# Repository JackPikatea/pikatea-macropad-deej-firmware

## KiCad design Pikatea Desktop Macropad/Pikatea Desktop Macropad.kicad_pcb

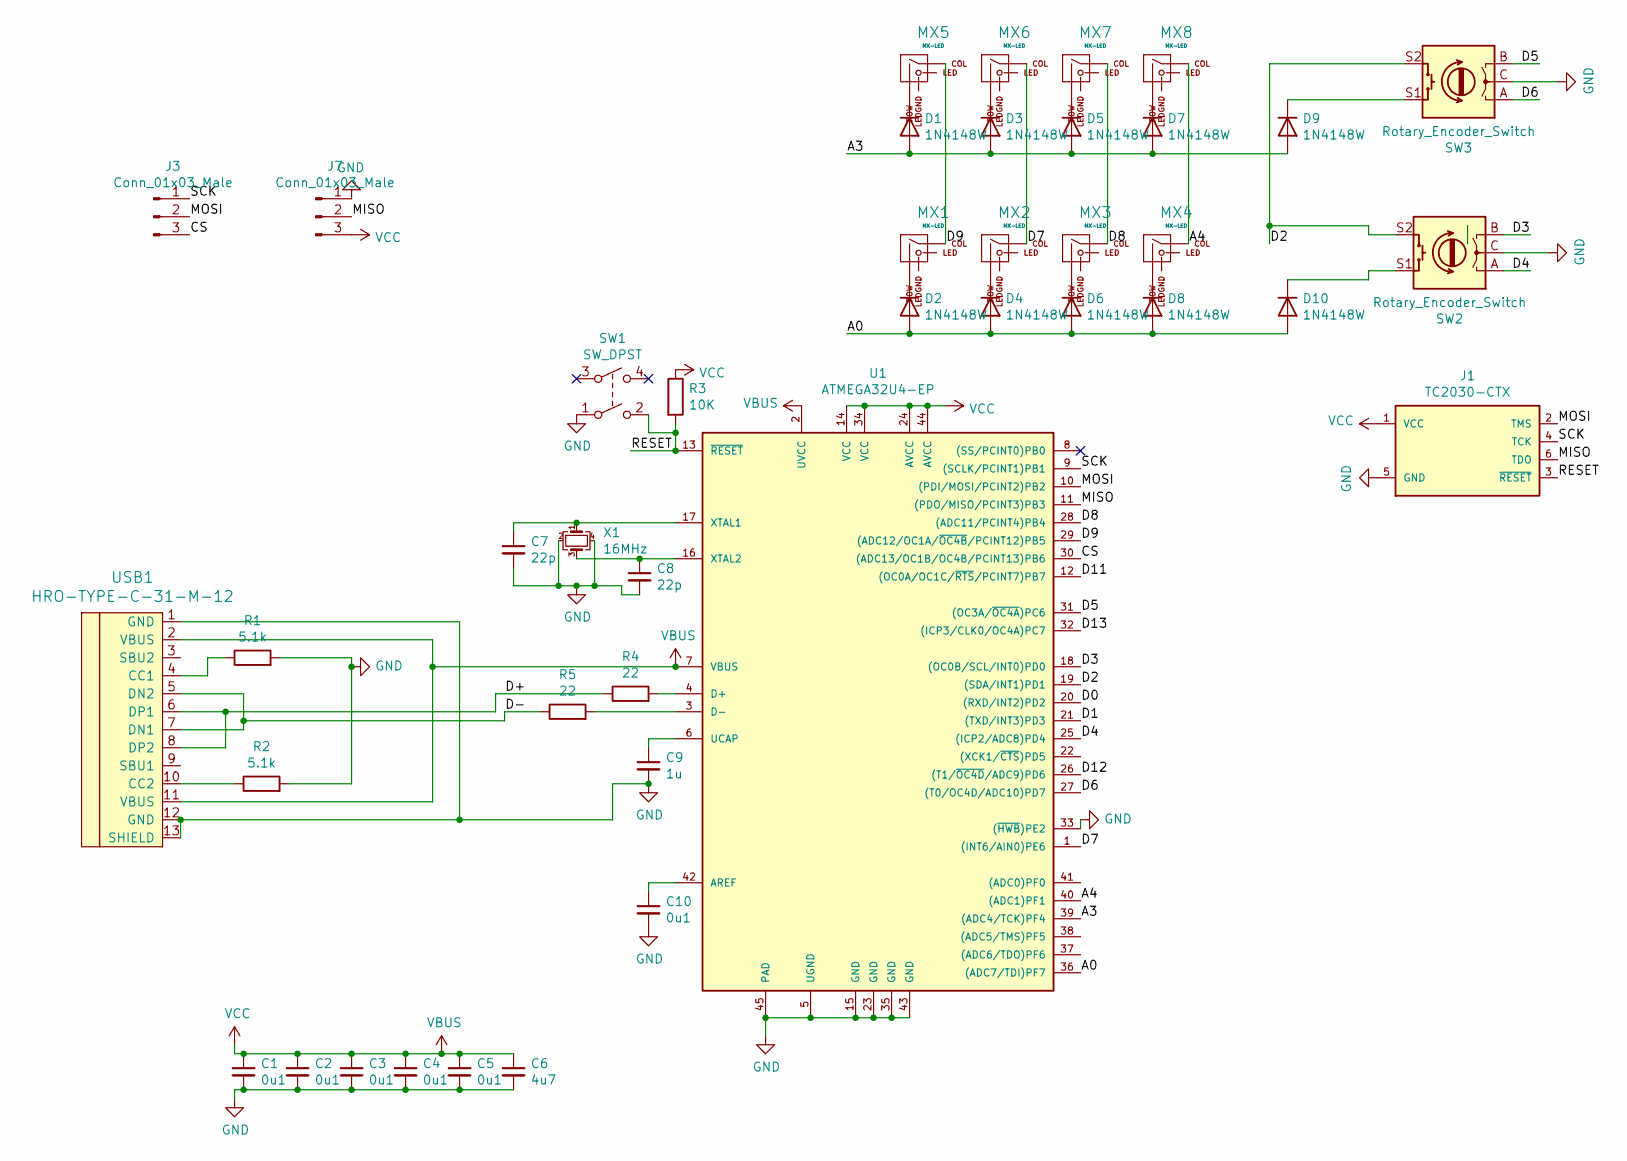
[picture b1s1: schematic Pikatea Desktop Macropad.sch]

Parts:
C1, C2, C3, C4, C5, C10: 0u1; C_0805_2012Metric
C6: 4u7; C_0805_2012Metric
C7, C8: 22p; C_0805_2012Metric
C9: 1u; C_0805_2012Metric
D1, D2, D3, D4, D5, D6, D7, D8, D9, D10: 1N4148W; D_SOD-123
J1: TC2030-CTX; TC2030-IDC
J3, J7: Conn_01x03_Male; PinHeader_1x03_P2.54mm_Vertical
MX1, MX2, MX3, MX4, MX5, MX6, MX7, MX8: MX-LED; MXOnly-1U
R1, R2: 5.1k; R_0805_2012Metric
R3: 10K; R_0805_2012Metric
R4, R5: 22; R_0805_2012Metric
SW1: SW_DPST; SW_SPST_TL3342
SW2, SW3: Rotary_Encoder_Switch; Encoder-BI_EN11_HSM0E
U1: ATMEGA32U4-EP; LQFP-44_10x10mm_P0.8mm
USB1: HRO-TYPE-C-31-M-12; HRO-TYPE-C-31-M-12-Assembly
X1: 16MHz; Crystal_SMD_SeikoEpson_FA238-4Pin_3.2x2.5mm

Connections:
/A0: D2.2 (A), D4.2 (A), D6.2 (A), D8.2 (A), D10.2 (A), U1.36 ((ADC7/TDI)PF7)
/A3: D1.2 (A), D3.2 (A), D5.2 (A), D7.2 (A), D9.2 (A), U1.39 ((ADC4/TCK)PF4)
/A4: MX4.1 (COL), MX8.1 (COL), U1.40 ((ADC1)PF1)
/CS: J3.3, U1.30 ((ADC13/OC1B/OC4B/PCINT13)PB6)
/D0: U1.20 ((RXD/INT2)PD2)
/D1: U1.21 ((TXD/INT3)PD3)
/D2: SW2.S2, SW3.S2, U1.19 ((SDA/INT1)PD1)
/D3: SW2.B, U1.18 ((OC0B/SCL/INT0)PD0)
/D4: SW2.A, U1.25 ((ICP2/ADC8)PD4)
/D5: SW3.B, U1.31 ((OC3A/~OC4A~)PC6)
/D6: SW3.A, U1.27 ((T0/OC4D/ADC10)PD7)
/D7: MX2.1 (COL), MX6.1 (COL), U1.1 ((INT6/AIN0)PE6)
/D8: MX3.1 (COL), MX7.1 (COL), U1.28 ((ADC11/PCINT4)PB4)
/D9: MX1.1 (COL), MX5.1 (COL), U1.29 ((ADC12/OC1A/~OC4B~/PCINT12)PB5)
/D11: U1.12 ((OC0A/OC1C/~RTS~/PCINT7)PB7)
/D12: U1.26 ((T1/~OC4D~/ADC9)PD6)
/D13: U1.32 ((ICP3/CLK0/OC4A)PC7)
/D+: R4.1, USB1.6 (DP1), USB1.8 (DP2)
/D-: R5.1, USB1.5 (DN2), USB1.7 (DN1)
/MISO: J1.6 (TDO), J7.2, U1.11 ((PDO/MISO/PCINT3)PB3)
/MOSI: J1.2 (TMS), J3.2, U1.10 ((PDI/MOSI/PCINT2)PB2)
/RESET: J1.3 (~RESET), R3.2, SW1.2, U1.13 (~RESET~)
/SCK: J1.4 (TCK), J3.1, U1.9 ((SCLK/PCINT1)PB1)
GND: C1.2, C2.2, C3.2, C4.2, C5.2, C6.2, C7.2, C8.2, C9.2, C10.2, J1.5 (GND), J7.1, R1.2, R2.2, SW1.1, SW2.C, SW3.C, U1.5 (UGND), U1.15 (GND), U1.23 (GND), U1.33 ((~HWB~)PE2), U1.35 (GND), U1.43 (GND), U1.45 (PAD), USB1.1 (GND), USB1.12 (GND), USB1.13 (SHIELD), X1.2, X1.4
unnamed: C7.1, U1.17 (XTAL1), X1.1
unnamed: C8.1, U1.16 (XTAL2), X1.3
unnamed: C9.1, U1.6 (UCAP)
unnamed: C10.1, U1.42 (AREF)
unnamed: D1.1 (K), MX5.2 (ROW)
unnamed: D2.1 (K), MX1.2 (ROW)
unnamed: D3.1 (K), MX6.2 (ROW)
unnamed: D4.1 (K), MX2.2 (ROW)
unnamed: D5.1 (K), MX7.2 (ROW)
unnamed: D6.1 (K), MX3.2 (ROW)
unnamed: D7.1 (K), MX8.2 (ROW)
unnamed: D8.1 (K), MX4.2 (ROW)
unnamed: D9.1 (K), SW3.S1
unnamed: D10.1 (K), SW2.S1
unnamed: R1.1, USB1.4 (CC1)
unnamed: R2.1, USB1.10 (CC2)
unnamed: R4.2, U1.4 (D+)
unnamed: R5.2, U1.3 (D-)
VBUS: C1.1, C2.1, C3.1, C4.1, C5.1, C6.1, J1.1 (VCC), J7.3, R3.1, U1.2 (UVCC), U1.7 (VBUS), U1.14 (VCC), U1.24 (AVCC), U1.34 (VCC), U1.44 (AVCC), USB1.2 (VBUS), USB1.11 (VBUS)

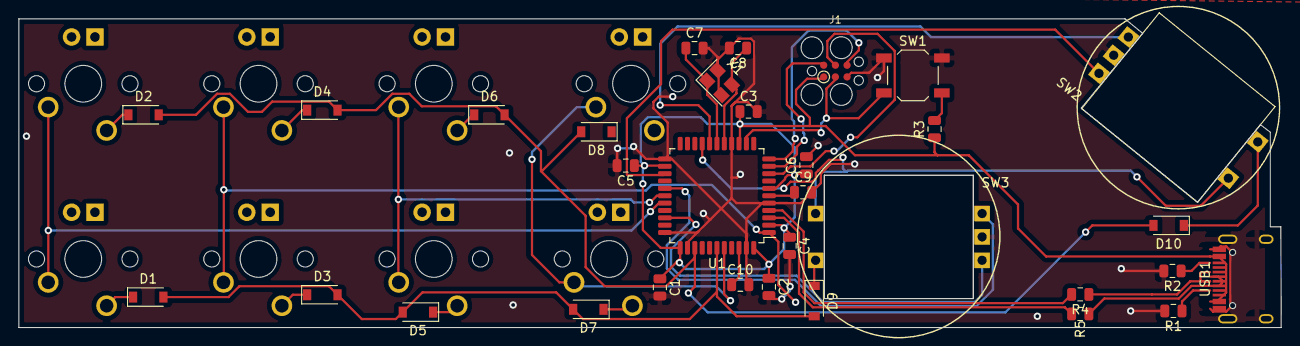
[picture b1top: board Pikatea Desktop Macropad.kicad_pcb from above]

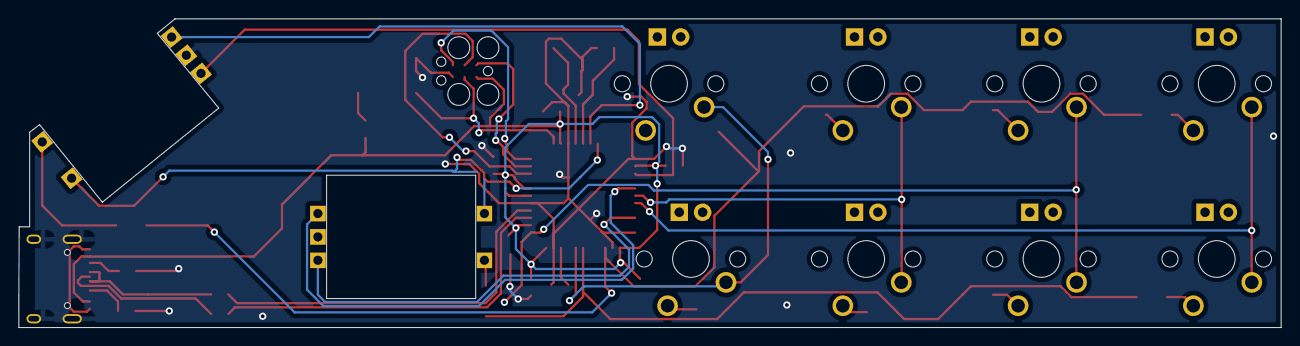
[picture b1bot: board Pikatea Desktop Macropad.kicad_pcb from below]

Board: 2 copper layers, 137.2 x 33.5 mm, 40 parts (8 on the bottom side), 37 nets.

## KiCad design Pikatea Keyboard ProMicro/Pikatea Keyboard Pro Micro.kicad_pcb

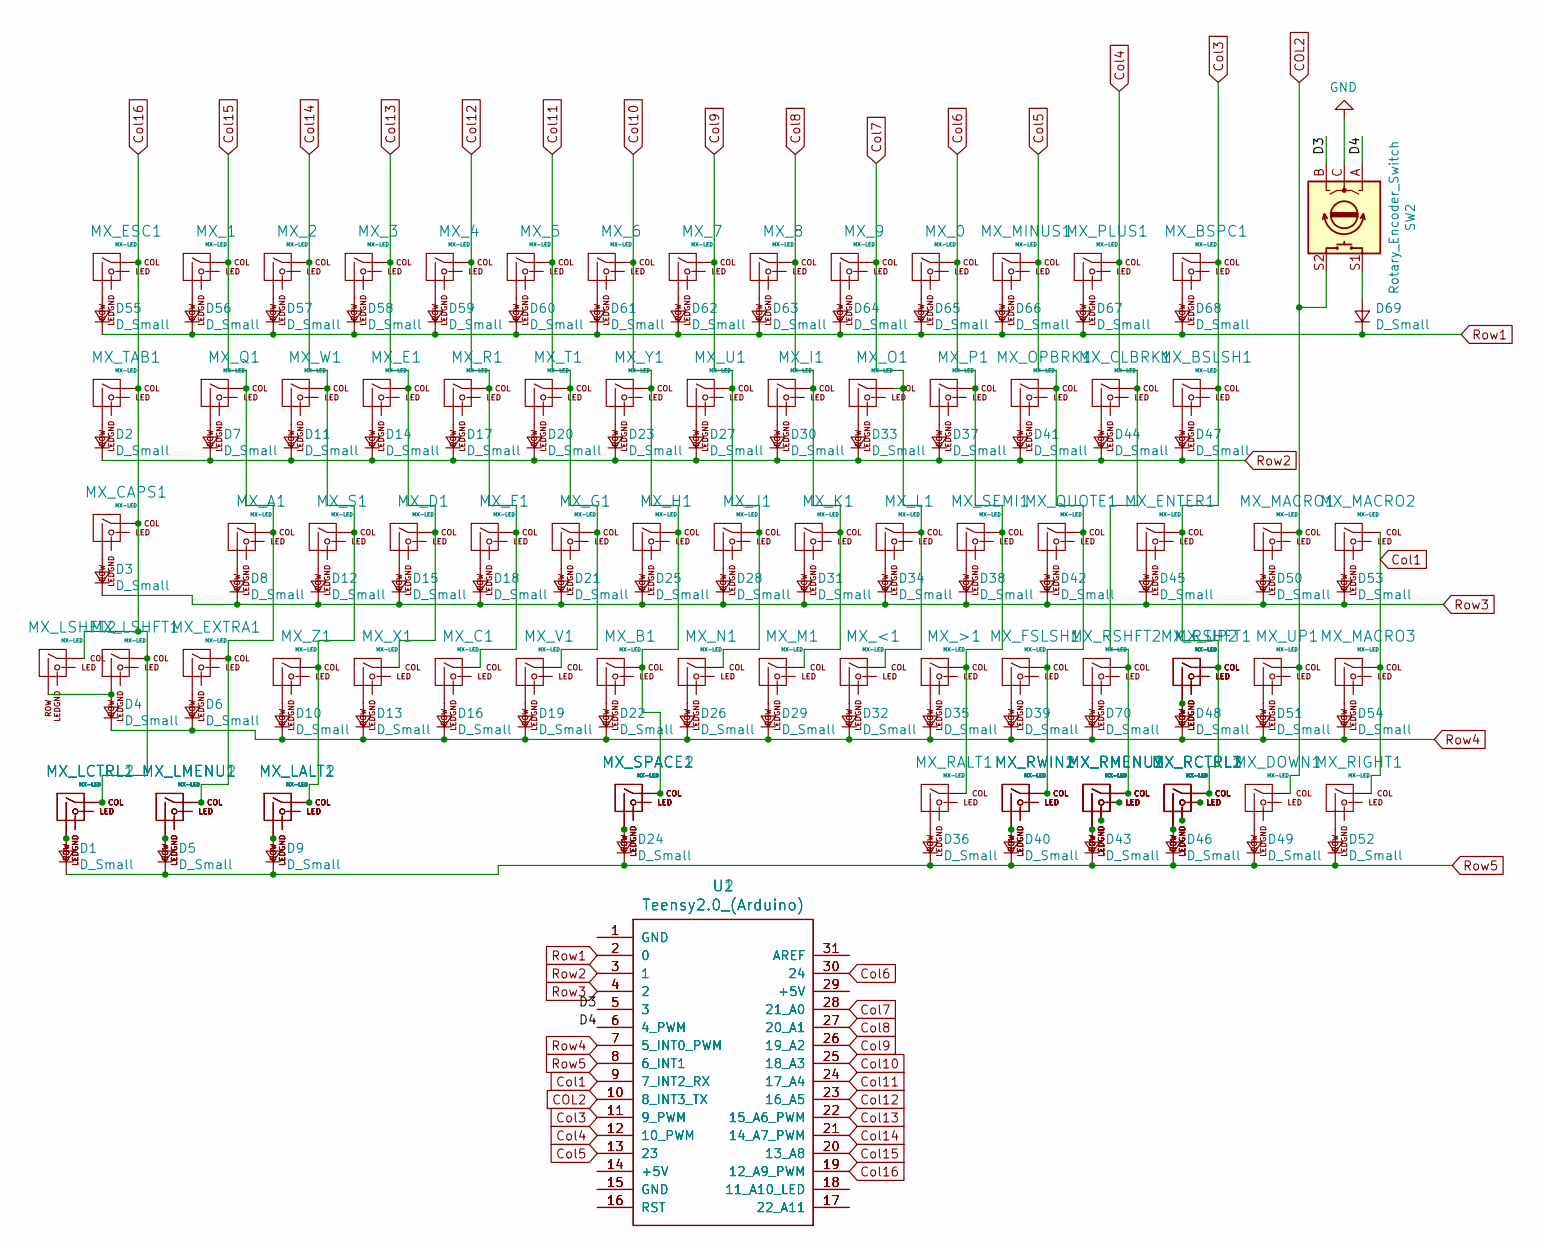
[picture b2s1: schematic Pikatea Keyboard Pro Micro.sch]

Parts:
D1, D2, D3, D4, D5, D6, D7, D8, D9, D10, D11, D12, D13, D14, D15, D16, D17, D18, D19, D20, D21, D22, D23, D24, D25, D26, D27, D28, D29, D30, D31, D32, D33, D34, D35, D36, D37, D38, D39, D40, D41, D42, D43, D44, D45, D46, D47, D48, D49, D50, D51, D52, D53, D54, D55, D56, D57, D58, D59, D60, D61, D62, D63, D64, D65, D66, D67, D68, D69, D70: D_Small; D_SOD-123
MX_0, MX_3, MX_4, MX_5, MX_6, MX_7, MX_8, MX_9: MX-LED; MXOnly-1U
MX_1, MX_2: MX-LED; MXOnly-1U-FLIPPED
MX_<1: MX-LED; MXOnly-1U
MX_>1: MX-LED; MXOnly-1U
MX_A1: MX-LED; MXOnly-1U-FLIPPED
MX_B1: MX-LED; MXOnly-1U
MX_BSLSH1: MX-LED; MXOnly-1.5U-FLIPPED
MX_BSPC1: MX-LED; MXOnly-2U-FLIPPED
MX_C1: MX-LED; MXOnly-1U
MX_CAPS1: MX-LED; MXOnly-1.75U-FLIPPED
MX_CLBRK1: MX-LED; MXOnly-1U
MX_D1: MX-LED; MXOnly-1U
MX_DOWN1: MX-LED; MXOnly-1U
MX_E1: MX-LED; MXOnly-1U
MX_ENTER1: MX-LED; MXOnly-2.25U-FLIPPED-ReversedStabilizers
MX_ESC1: MX-LED; MXOnly-1U-FLIPPED
MX_EXTRA1: MX-LED; MXOnly-1U-FLIPPED
MX_F1: MX-LED; MXOnly-1U
MX_FSLSH1: MX-LED; MXOnly-1U
MX_G1: MX-LED; MXOnly-1U
MX_H1: MX-LED; MXOnly-1U
MX_I1: MX-LED; MXOnly-1U
MX_J1: MX-LED; MXOnly-1U
MX_K1: MX-LED; MXOnly-1U
MX_L1: MX-LED; MXOnly-1U
MX_LALT1: MX-LED; MXOnly-1.25U-FLIPPED
MX_LALT2: MX-LED; MXOnly-1.5U-FLIPPED
MX_LCTRL1: MX-LED; MXOnly-1.25U-FLIPPED
MX_LCTRL2: MX-LED; MXOnly-1.5U-FLIPPED
MX_LMENU1: MX-LED; MXOnly-1.25U-FLIPPED
MX_LMENU2: MX-LED; MXOnly-1U-FLIPPED
MX_LSHFT1: MX-LED; MXOnly-2.25U-FLIPPED-ReversedStabilizers
MX_LSHFT2: MX-LED; MXOnly-1.25U-FLIPPED
MX_M1: MX-LED; MXOnly-1U
MX_MACRO1, MX_MACRO2, MX_MACRO3: MX-LED; MXOnly-1U
MX_MINUS1: MX-LED; MXOnly-1U
MX_N1: MX-LED; MXOnly-1U
MX_O1: MX-LED; MXOnly-1U
MX_OPBRK1: MX-LED; MXOnly-1U
MX_P1: MX-LED; MXOnly-1U
MX_PLUS1: MX-LED; MXOnly-1U
MX_Q1: MX-LED; MXOnly-1U-FLIPPED
MX_QUOTE1: MX-LED; MXOnly-1U
MX_R1: MX-LED; MXOnly-1U
MX_RALT1: MX-LED; MXOnly-1.25U-FLIPPED
MX_RCTRL1: MX-LED; MXOnly-1.25U-FLIPPED
MX_RCTRL2: MX-LED; MXOnly-1.5U-FLIPPED
MX_RCTRL3: MX-LED; MXOnly-1U
MX_RIGHT1: MX-LED; MXOnly-1U
MX_RMENU1: MX-LED; MXOnly-1.25U-FLIPPED
MX_RMENU2: MX-LED; MXOnly-1.5U-FLIPPED
MX_RMENU3: MX-LED; MXOnly-1U-FLIPPED
MX_RSHFT1: MX-LED; MXOnly-2.75U-FLIPPED-ReversedStabilizers
MX_RSHFT2: MX-LED; MXOnly-1.75U-FLIPPED
MX_RWIN1: MX-LED; MXOnly-1.25U-FLIPPED
MX_RWIN2: MX-LED; MXOnly-1U-FLIPPED
MX_S1: MX-LED; MXOnly-1U
MX_SEMI1: MX-LED; MXOnly-1U
MX_SPACE1: MX-LED; MXOnly-6.25U-FLIPPED-ReversedStabilizers
MX_SPACE2: MX-LED; MXOnly-7U-FLIPPED-ReversedStabilizers
MX_T1: MX-LED; MXOnly-1U
MX_TAB1: MX-LED; MXOnly-1.5U-FLIPPED
MX_U1: MX-LED; MXOnly-1U
MX_UP1, MX_UP2: MX-LED; MXOnly-1U
MX_V1: MX-LED; MXOnly-1U
MX_W1: MX-LED; MXOnly-1U
MX_X1: MX-LED; MXOnly-1U
MX_Y1: MX-LED; MXOnly-1U
MX_Z1: MX-LED; MXOnly-1U
SW2: Rotary_Encoder_Switch; Encoder-BI_EN11_HSM0E
U1, U2: Teensy2.0_(Arduino); Teensy2.0

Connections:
/D3: SW2.B, U1.5 (3), U2.5 (3)
/D4: SW2.A, U1.6 (4_PWM), U2.6 (4_PWM)
COL2: MX_DOWN1.1 (COL), MX_MACRO1.1 (COL), MX_UP1.1 (COL), SW2.S2, U1.10 (8_INT3_TX), U2.10 (8_INT3_TX)
Col1: MX_MACRO2.1 (COL), MX_MACRO3.1 (COL), MX_RIGHT1.1 (COL), U1.9 (7_INT2_RX), U2.9 (7_INT2_RX)
Col3: MX_BSLSH1.1 (COL), MX_BSPC1.1 (COL), MX_ENTER1.1 (COL), MX_RCTRL1.1 (COL), MX_RCTRL2.1 (COL), MX_RCTRL3.1 (COL), MX_RSHFT1.1 (COL), MX_UP2.1 (COL), U1.11 (9_PWM), U2.11 (9_PWM)
Col4: MX_CLBRK1.1 (COL), MX_PLUS1.1 (COL), MX_RMENU1.1 (COL), MX_RMENU2.1 (COL), MX_RMENU3.1 (COL), MX_RSHFT2.1 (COL), U1.12 (10_PWM), U2.12 (10_PWM)
Col5: MX_FSLSH1.1 (COL), MX_MINUS1.1 (COL), MX_OPBRK1.1 (COL), MX_QUOTE1.1 (COL), MX_RWIN1.1 (COL), MX_RWIN2.1 (COL), U1.13 (23), U2.13 (23)
Col6: MX_0.1 (COL), MX_>1.1 (COL), MX_P1.1 (COL), MX_RALT1.1 (COL), MX_SEMI1.1 (COL), U1.30 (24), U2.30 (24)
Col7: MX_9.1 (COL), MX_<1.1 (COL), MX_L1.1 (COL), MX_O1.1 (COL), U1.28 (21_A0), U2.28 (21_A0)
Col8: MX_8.1 (COL), MX_I1.1 (COL), MX_K1.1 (COL), MX_M1.1 (COL), U1.27 (20_A1), U2.27 (20_A1)
Col9: MX_7.1 (COL), MX_J1.1 (COL), MX_N1.1 (COL), MX_U1.1 (COL), U1.26 (19_A2), U2.26 (19_A2)
Col10: MX_6.1 (COL), MX_B1.1 (COL), MX_H1.1 (COL), MX_SPACE1.1 (COL), MX_SPACE2.1 (COL), MX_Y1.1 (COL), U1.25 (18_A3), U2.25 (18_A3)
Col11: MX_5.1 (COL), MX_G1.1 (COL), MX_T1.1 (COL), MX_V1.1 (COL), U1.24 (17_A4), U2.24 (17_A4)
Col12: MX_4.1 (COL), MX_C1.1 (COL), MX_F1.1 (COL), MX_R1.1 (COL), U1.23 (16_A5), U2.23 (16_A5)
Col13: MX_3.1 (COL), MX_D1.1 (COL), MX_E1.1 (COL), MX_X1.1 (COL), U1.22 (15_A6_PWM), U2.22 (15_A6_PWM)
Col14: MX_2.1 (COL), MX_LALT1.1 (COL), MX_LALT2.1 (COL), MX_S1.1 (COL), MX_W1.1 (COL), MX_Z1.1 (COL), U1.21 (14_A7_PWM), U2.21 (14_A7_PWM)
Col15: MX_1.1 (COL), MX_A1.1 (COL), MX_EXTRA1.1 (COL), MX_LMENU1.1 (COL), MX_LMENU2.1 (COL), MX_Q1.1 (COL), U1.20 (13_A8), U2.20 (13_A8)
Col16: MX_CAPS1.1 (COL), MX_ESC1.1 (COL), MX_LCTRL1.1 (COL), MX_LCTRL2.1 (COL), MX_LSHFT1.1 (COL), MX_LSHFT2.1 (COL), MX_TAB1.1 (COL), U1.19 (12_A9_PWM), U2.19 (12_A9_PWM)
GND: SW2.C
unnamed: D1.2 (A), MX_LCTRL1.2 (ROW), MX_LCTRL2.2 (ROW)
unnamed: D2.2 (A), MX_TAB1.2 (ROW)
unnamed: D3.2 (A), MX_CAPS1.2 (ROW)
unnamed: D4.2 (A), MX_LSHFT1.2 (ROW), MX_LSHFT2.2 (ROW)
unnamed: D5.2 (A), MX_LMENU1.2 (ROW), MX_LMENU2.2 (ROW)
unnamed: D6.2 (A), MX_EXTRA1.2 (ROW)
unnamed: D7.2 (A), MX_Q1.2 (ROW)
unnamed: D8.2 (A), MX_A1.2 (ROW)
unnamed: D9.2 (A), MX_LALT1.2 (ROW), MX_LALT2.2 (ROW)
unnamed: D10.2 (A), MX_Z1.2 (ROW)
unnamed: D11.2 (A), MX_W1.2 (ROW)
unnamed: D12.2 (A), MX_S1.2 (ROW)
unnamed: D13.2 (A), MX_X1.2 (ROW)
unnamed: D14.2 (A), MX_E1.2 (ROW)
unnamed: D15.2 (A), MX_D1.2 (ROW)
unnamed: D16.2 (A), MX_C1.2 (ROW)
unnamed: D17.2 (A), MX_R1.2 (ROW)
unnamed: D18.2 (A), MX_F1.2 (ROW)
unnamed: D19.2 (A), MX_V1.2 (ROW)
unnamed: D20.2 (A), MX_T1.2 (ROW)
unnamed: D21.2 (A), MX_G1.2 (ROW)
unnamed: D22.2 (A), MX_B1.2 (ROW)
unnamed: D23.2 (A), MX_Y1.2 (ROW)
unnamed: D24.2 (A), MX_SPACE1.2 (ROW), MX_SPACE2.2 (ROW)
unnamed: D25.2 (A), MX_H1.2 (ROW)
unnamed: D26.2 (A), MX_N1.2 (ROW)
unnamed: D27.2 (A), MX_U1.2 (ROW)
unnamed: D28.2 (A), MX_J1.2 (ROW)
unnamed: D29.2 (A), MX_M1.2 (ROW)
unnamed: D30.2 (A), MX_I1.2 (ROW)
unnamed: D31.2 (A), MX_K1.2 (ROW)
unnamed: D32.2 (A), MX_<1.2 (ROW)
unnamed: D33.2 (A), MX_O1.2 (ROW)
unnamed: D34.2 (A), MX_L1.2 (ROW)
unnamed: D35.2 (A), MX_>1.2 (ROW)
unnamed: D36.2 (A), MX_RALT1.2 (ROW)
unnamed: D37.2 (A), MX_P1.2 (ROW)
unnamed: D38.2 (A), MX_SEMI1.2 (ROW)
unnamed: D39.2 (A), MX_FSLSH1.2 (ROW)
unnamed: D40.2 (A), MX_RWIN1.2 (ROW), MX_RWIN2.2 (ROW)
unnamed: D41.2 (A), MX_OPBRK1.2 (ROW)
unnamed: D42.2 (A), MX_QUOTE1.2 (ROW)
unnamed: D43.2 (A), MX_RMENU1.2 (ROW), MX_RMENU2.2 (ROW), MX_RMENU3.2 (ROW)
unnamed: D44.2 (A), MX_CLBRK1.2 (ROW)
unnamed: D45.2 (A), MX_ENTER1.2 (ROW)
unnamed: D46.2 (A), MX_RCTRL1.2 (ROW), MX_RCTRL2.2 (ROW), MX_RCTRL3.2 (ROW)
unnamed: D47.2 (A), MX_BSLSH1.2 (ROW)
unnamed: D48.2 (A), MX_RSHFT1.2 (ROW), MX_UP2.2 (ROW)
unnamed: D49.2 (A), MX_DOWN1.2 (ROW)
unnamed: D50.2 (A), MX_MACRO1.2 (ROW)
unnamed: D51.2 (A), MX_UP1.2 (ROW)
unnamed: D52.2 (A), MX_RIGHT1.2 (ROW)
unnamed: D53.2 (A), MX_MACRO2.2 (ROW)
unnamed: D54.2 (A), MX_MACRO3.2 (ROW)
unnamed: D55.2 (A), MX_ESC1.2 (ROW)
unnamed: D56.2 (A), MX_1.2 (ROW)
unnamed: D57.2 (A), MX_2.2 (ROW)
unnamed: D58.2 (A), MX_3.2 (ROW)
unnamed: D59.2 (A), MX_4.2 (ROW)
unnamed: D60.2 (A), MX_5.2 (ROW)
unnamed: D61.2 (A), MX_6.2 (ROW)
unnamed: D62.2 (A), MX_7.2 (ROW)
unnamed: D63.2 (A), MX_8.2 (ROW)
unnamed: D64.2 (A), MX_9.2 (ROW)
unnamed: D65.2 (A), MX_0.2 (ROW)
unnamed: D66.2 (A), MX_MINUS1.2 (ROW)
unnamed: D67.2 (A), MX_PLUS1.2 (ROW)
unnamed: D68.2 (A), MX_BSPC1.2 (ROW)
unnamed: D69.2 (A), SW2.S1
unnamed: D70.2 (A), MX_RSHFT2.2 (ROW)
unnamed: MX_LALT1.3 (LED), MX_LALT2.3 (LED)
unnamed: MX_LALT1.4 (LEDGND), MX_LALT2.4 (LEDGND)
unnamed: MX_LCTRL1.3 (LED), MX_LCTRL2.3 (LED)
unnamed: MX_LCTRL1.4 (LEDGND), MX_LCTRL2.4 (LEDGND)
unnamed: MX_LMENU1.3 (LED), MX_LMENU2.3 (LED)
unnamed: MX_LMENU1.4 (LEDGND), MX_LMENU2.4 (LEDGND)
unnamed: MX_RCTRL1.3 (LED), MX_RCTRL2.3 (LED), MX_RCTRL3.3 (LED)
unnamed: MX_RCTRL1.4 (LEDGND), MX_RCTRL2.4 (LEDGND), MX_RCTRL3.4 (LEDGND)
unnamed: MX_RMENU1.3 (LED), MX_RMENU2.3 (LED), MX_RMENU3.3 (LED)
unnamed: MX_RMENU1.4 (LEDGND), MX_RMENU2.4 (LEDGND), MX_RMENU3.4 (LEDGND)
unnamed: MX_RSHFT1.3 (LED), MX_UP2.3 (LED)
unnamed: MX_RSHFT1.4 (LEDGND), MX_UP2.4 (LEDGND)
unnamed: MX_RWIN1.3 (LED), MX_RWIN2.3 (LED)
unnamed: MX_RWIN1.4 (LEDGND), MX_RWIN2.4 (LEDGND)
unnamed: MX_SPACE1.3 (LED), MX_SPACE2.3 (LED)
unnamed: MX_SPACE1.4 (LEDGND), MX_SPACE2.4 (LEDGND)
unnamed: U1.1 (GND), U2.1 (GND)
unnamed: U1.14 (+5V), U2.14 (+5V)
unnamed: U1.15 (GND), U2.15 (GND)
unnamed: U1.16 (RST), U2.16 (RST)
unnamed: U1.17 (22_A11), U2.17 (22_A11)
unnamed: U1.18 (11_A10_LED), U2.18 (11_A10_LED)
unnamed: U1.29 (+5V), U2.29 (+5V)
unnamed: U1.31 (AREF), U2.31 (AREF)
Row1: D55.1 (K), D56.1 (K), D57.1 (K), D58.1 (K), D59.1 (K), D60.1 (K), D61.1 (K), D62.1 (K), D63.1 (K), D64.1 (K), D65.1 (K), D66.1 (K), D67.1 (K), D68.1 (K), D69.1 (K), U1.2 (0), U2.2 (0)
Row2: D2.1 (K), D7.1 (K), D11.1 (K), D14.1 (K), D17.1 (K), D20.1 (K), D23.1 (K), D27.1 (K), D30.1 (K), D33.1 (K), D37.1 (K), D41.1 (K), D44.1 (K), D47.1 (K), U1.3 (1), U2.3 (1)
Row3: D3.1 (K), D8.1 (K), D12.1 (K), D15.1 (K), D18.1 (K), D21.1 (K), D25.1 (K), D28.1 (K), D31.1 (K), D34.1 (K), D38.1 (K), D42.1 (K), D45.1 (K), D50.1 (K), D53.1 (K), U1.4 (2), U2.4 (2)
Row4: D4.1 (K), D6.1 (K), D10.1 (K), D13.1 (K), D16.1 (K), D19.1 (K), D22.1 (K), D26.1 (K), D29.1 (K), D32.1 (K), D35.1 (K), D39.1 (K), D48.1 (K), D51.1 (K), D54.1 (K), D70.1 (K), U1.7 (5_INT0_PWM), U2.7 (5_INT0_PWM)
Row5: D1.1 (K), D5.1 (K), D9.1 (K), D24.1 (K), D36.1 (K), D40.1 (K), D43.1 (K), D46.1 (K), D49.1 (K), D52.1 (K), U1.8 (6_INT1), U2.8 (6_INT1)

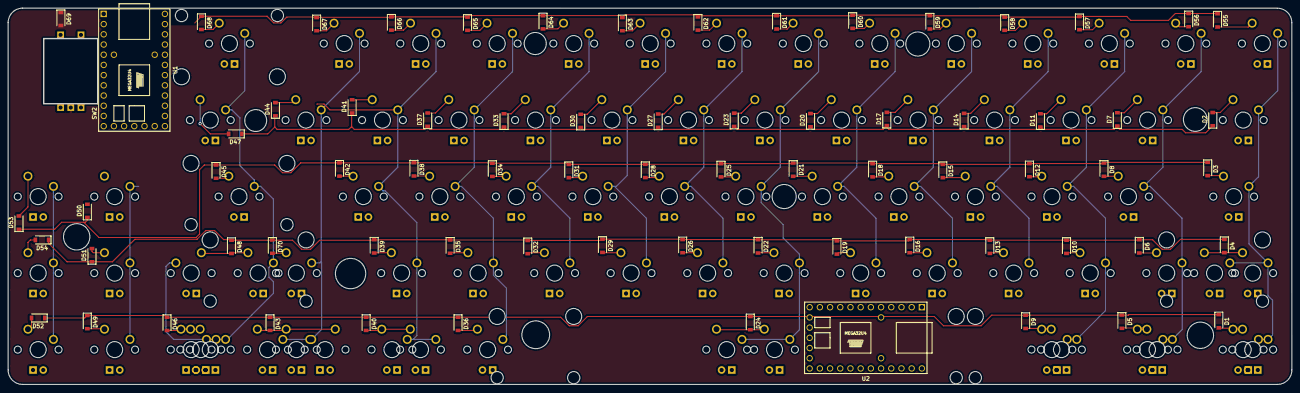
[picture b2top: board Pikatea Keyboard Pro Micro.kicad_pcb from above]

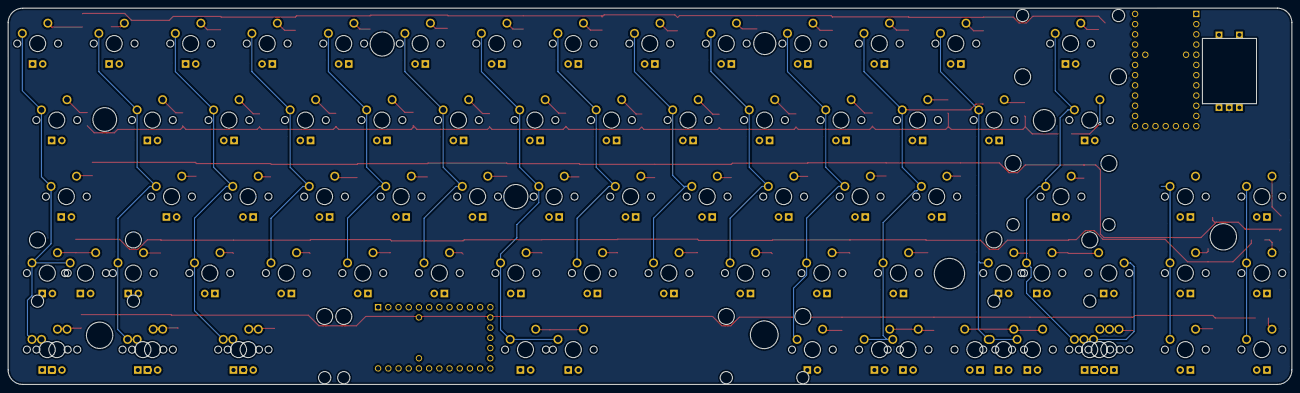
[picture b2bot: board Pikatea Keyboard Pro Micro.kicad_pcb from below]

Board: 2 copper layers, 319.6 x 93.7 mm, 153 parts (78 on the bottom side), 117 nets.

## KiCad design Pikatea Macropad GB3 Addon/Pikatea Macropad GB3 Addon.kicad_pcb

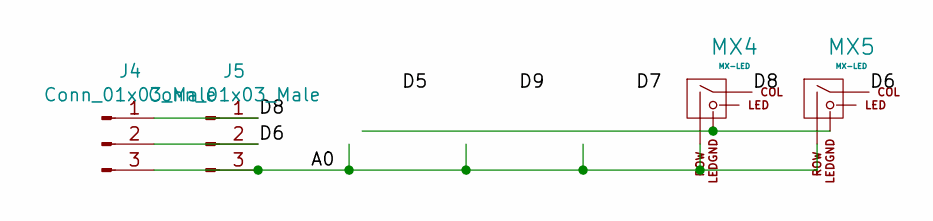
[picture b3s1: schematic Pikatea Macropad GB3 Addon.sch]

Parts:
J4, J5: Conn_01x03_Male; PinHeader_1x03_P2.54mm_Vertical
MX4, MX5: MX-LED; MXOnly-1U

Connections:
/A0: J4.3, J5.3, MX4.2 (ROW), MX5.2 (ROW)
/D6: J4.2, J5.2, MX5.1 (COL)
/D8: J4.1, J5.1, MX4.1 (COL)
unnamed: MX4.4 (LEDGND), MX5.4 (LEDGND)

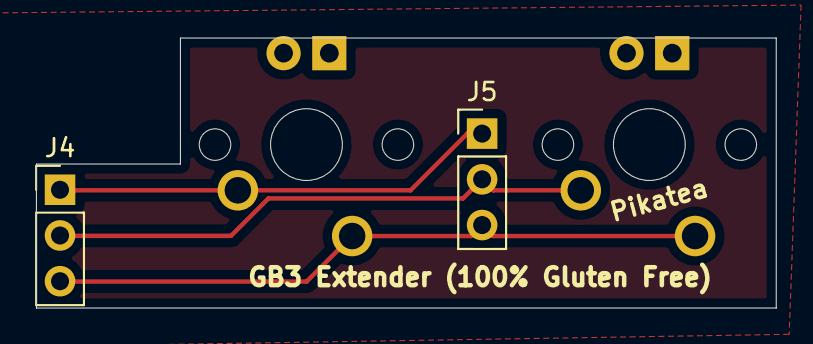
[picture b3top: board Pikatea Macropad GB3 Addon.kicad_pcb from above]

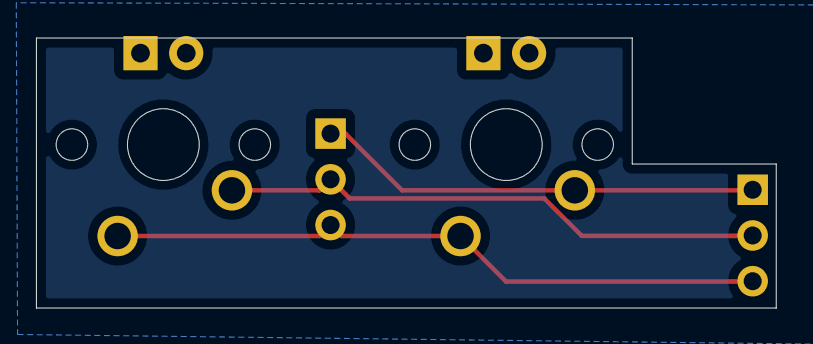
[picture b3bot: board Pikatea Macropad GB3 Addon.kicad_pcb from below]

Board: 2 copper layers, 41.1 x 15.0 mm, 4 parts (2 on the bottom side), 4 nets.

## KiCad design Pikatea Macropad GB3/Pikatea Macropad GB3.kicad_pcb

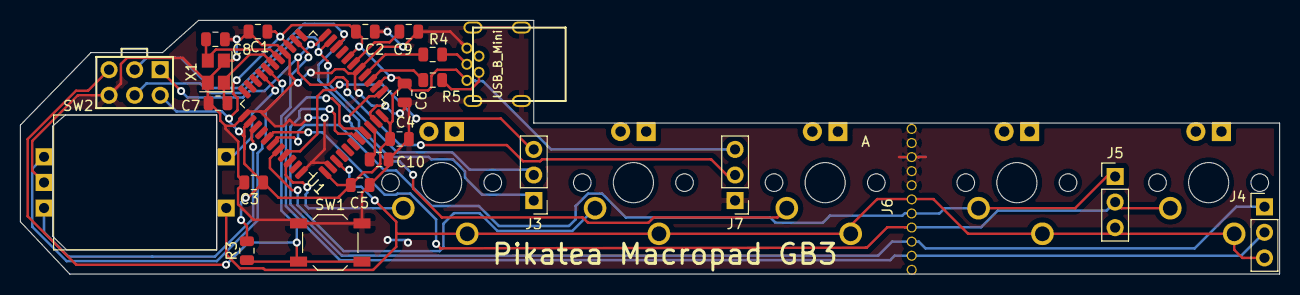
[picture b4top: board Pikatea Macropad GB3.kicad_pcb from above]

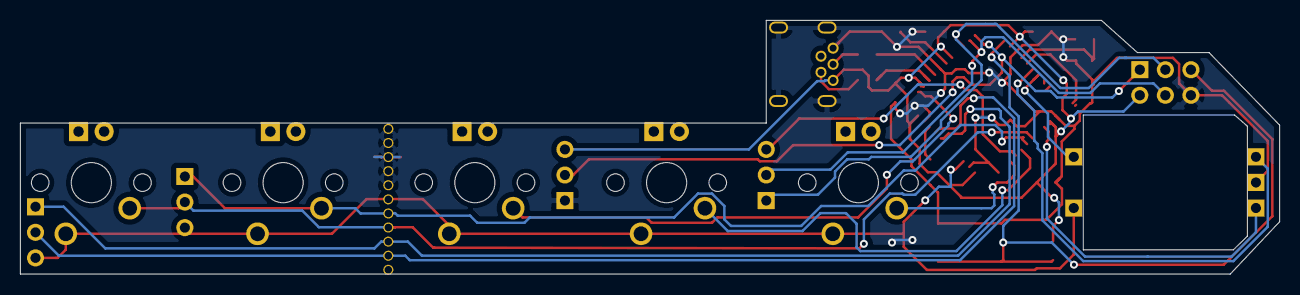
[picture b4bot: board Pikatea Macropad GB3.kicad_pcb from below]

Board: 2 copper layers, 125.1 x 25.2 mm, 29 parts (5 on the bottom side), 27 nets.

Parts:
C1, C2, C3, C4, C5, C10: 0u1; C_0805_2012Metric
C6: 4u7; C_0805_2012Metric
C7, C8: 22p; C_0805_2012Metric
C9: 1u; C_0805_2012Metric
J1: AVR-ISP-6; AVR_ICSP_3x2
J2: USB_B_Mini; USB-Mini-B_ LCSC-C46398
J3, J4, J5, J7: Conn_01x03_Male; PinHeader_1x03_P2.54mm_Vertical
J6: Conn_01x06_Male; Breakaway-Throughole
MX1, MX2, MX3, MX4, MX5: MX-LED; MXOnly-1U
R3: 10K; R_0805_2012Metric
R4, R5: 22; R_0805_2012Metric
SW1: SW_DPST; SW_SPST_TL3342
SW2: Rotary_Encoder_Switch; Encoder-BI_EN11_HSM0E
U1: ATMEGA32U4-EP; LQFP-44_10x10mm_P0.8mm
X1: 16MHz; Crystal_SMD_SeikoEpson_FA238-4Pin_3.2x2.5mm

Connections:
/A0: J4.3, J5.3, J6.4, MX1.2, MX2.2, MX3.2, MX4.2, MX5.2, SW2.S2, U1.36
/CS: J3.3, U1.30
/D0: J4.2, J6.6, U1.41
/D1: J4.1, J6.5, U1.40
/D2: SW2.S1, U1.19
/D3: SW2.B, U1.18
/D4: SW2.A, U1.25
/D5: MX1.1, U1.31
/D6: J5.2, J6.3, MX5.1, U1.27
/D7: MX3.1, U1.1
/D8: J5.1, J6.2, MX4.1, U1.28
/D9: MX2.1, U1.29
/D+: J2.3, R4.1
/D-: J2.2, R5.1
/MISO: J1.1, J7.2, U1.11
/MOSI: J1.4, J3.2, U1.10
/RESET: J1.5, R3.2, SW1.2, U1.13
/SCK: J1.3, J3.1, U1.9
GND: C1.2, C2.2, C3.2, C4.2, C5.2, C6.2, C7.2, C8.2, C9.2, C10.2, J1.6, J2.5, J2.6, J6.1, J7.1, SW1.1, SW2.C, U1.5, U1.15, U1.23, U1.33, U1.35, U1.43, X1.2, X1.4
unnamed: C7.1, U1.17, X1.1
unnamed: C8.1, U1.16, X1.3
unnamed: C9.1, U1.6
unnamed: C10.1, U1.42
unnamed: MX1.4, MX2.4, MX3.4, MX4.4, MX5.4
unnamed: R4.2, U1.4
unnamed: R5.2, U1.3
VBUS: C1.1, C2.1, C3.1, C4.1, C5.1, C6.1, J1.2, J2.1, J7.3, R3.1, U1.2, U1.7, U1.14, U1.24, U1.34, U1.44

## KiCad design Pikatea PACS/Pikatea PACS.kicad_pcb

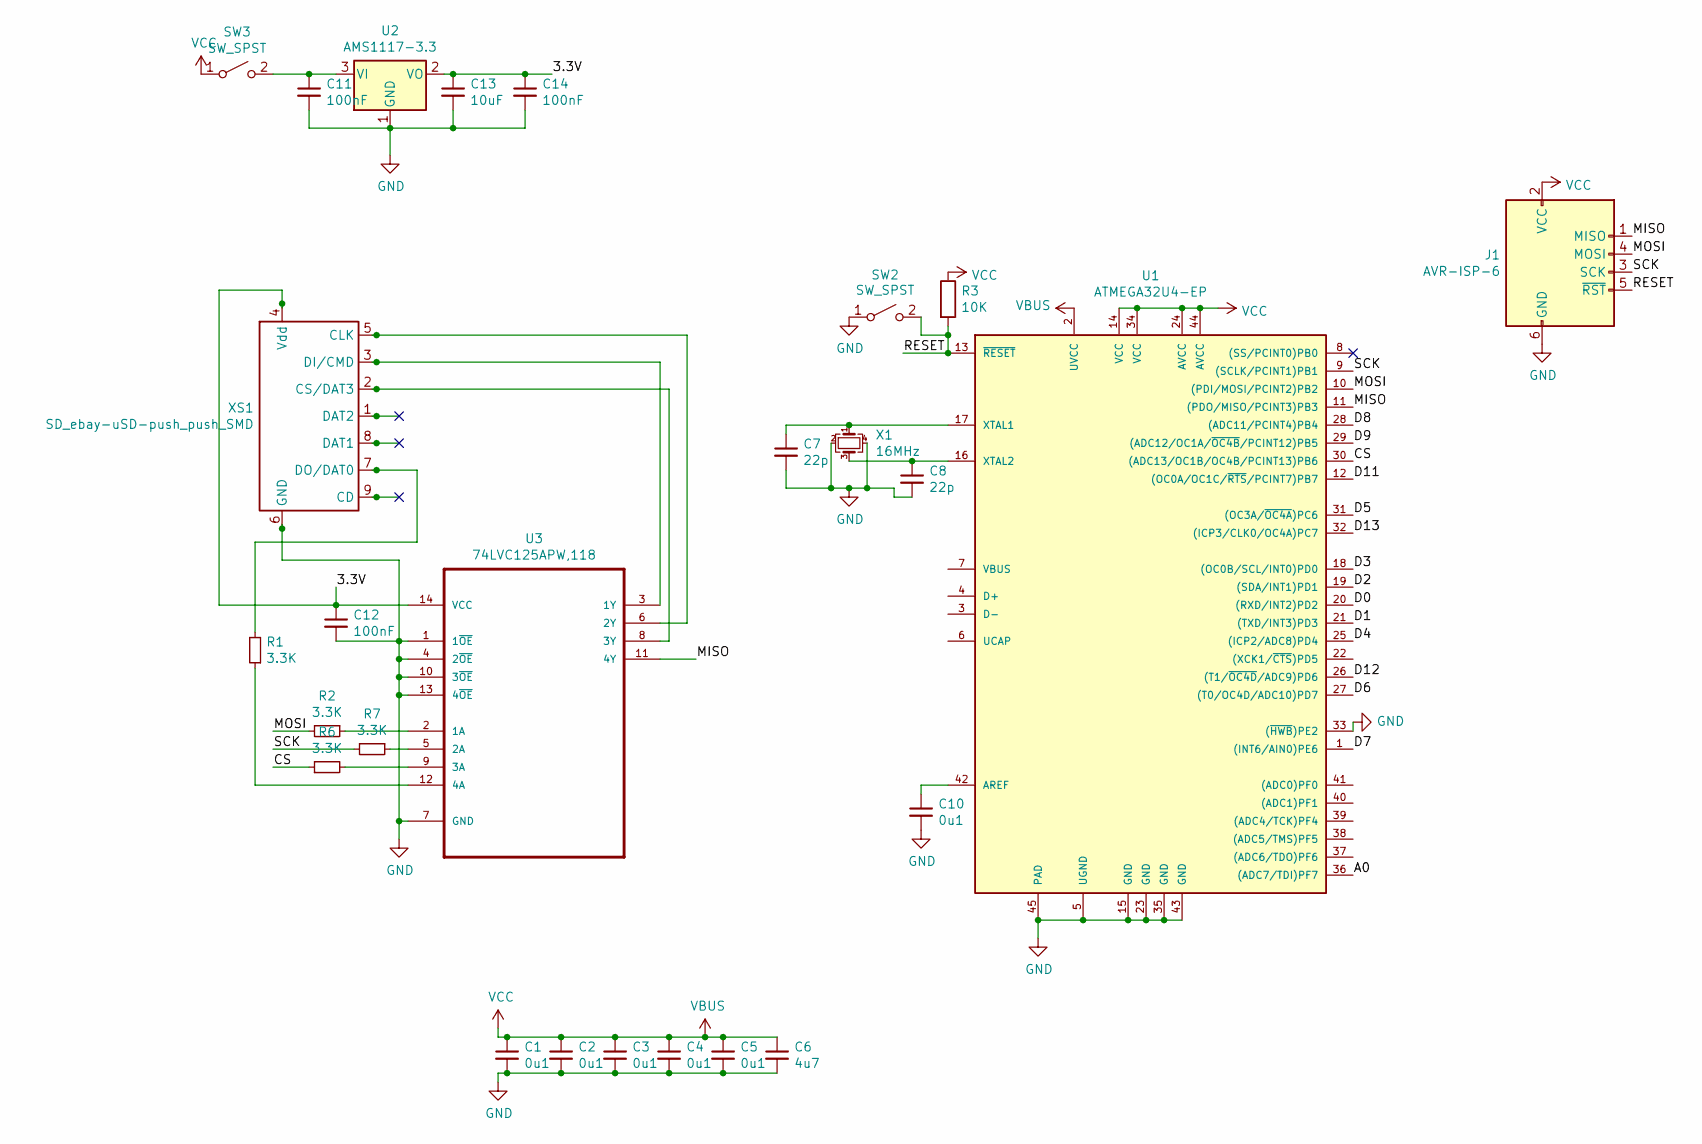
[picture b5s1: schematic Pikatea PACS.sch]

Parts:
C1, C2, C3, C4, C5, C10: 0u1; C_0805_2012Metric
C6: 4u7; C_0805_2012Metric
C7, C8: 22p; C_0805_2012Metric
C11, C12, C14: 100nF; C_0805_2012Metric
C13: 10uF; C_0805_2012Metric
J1: AVR-ISP-6; IDC-Header_2x03_P2.54mm_Vertical
R1, R2, R6, R7: 3.3K; R_0805_2012Metric
R3: 10K; R_0805_2012Metric
SW2: SW_SPST; SW_SPST_TL3342
SW3: SW_SPST; Pikatea_Solder_switch
U1: ATMEGA32U4-EP; LQFP-44_10x10mm_P0.8mm
U2: AMS1117-3.3; SOT-223-3_TabPin2
U3: 74LVC125APW,118; TSSOP-14-1EP_4.4x5mm_P0.65mm
X1: 16MHz; Crystal_SMD_SeikoEpson_FA238-4Pin_3.2x2.5mm
XS1: SD_ebay-uSD-push_push_SMD; XUNPU_TF-110

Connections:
/3.3V: C12.1, C13.1, C14.1, U2.2 (VO), U3.14 (VCC), XS1.4 (Vdd)
/A0: U1.36 ((ADC7/TDI)PF7)
/CS: R6.1, U1.30 ((ADC13/OC1B/OC4B/PCINT13)PB6)
/D0: U1.20 ((RXD/INT2)PD2)
/D1: U1.21 ((TXD/INT3)PD3)
/D2: U1.19 ((SDA/INT1)PD1)
/D3: U1.18 ((OC0B/SCL/INT0)PD0)
/D4: U1.25 ((ICP2/ADC8)PD4)
/D5: U1.31 ((OC3A/~OC4A~)PC6)
/D6: U1.27 ((T0/OC4D/ADC10)PD7)
/D7: U1.1 ((INT6/AIN0)PE6)
/D8: U1.28 ((ADC11/PCINT4)PB4)
/D9: U1.29 ((ADC12/OC1A/~OC4B~/PCINT12)PB5)
/D11: U1.12 ((OC0A/OC1C/~RTS~/PCINT7)PB7)
/D12: U1.26 ((T1/~OC4D~/ADC9)PD6)
/D13: U1.32 ((ICP3/CLK0/OC4A)PC7)
/MISO: J1.1 (MISO), U1.11 ((PDO/MISO/PCINT3)PB3), U3.11 (4Y)
/MOSI: J1.4 (MOSI), R2.2, U1.10 ((PDI/MOSI/PCINT2)PB2)
/RESET: J1.5 (~RST), R3.2, SW2.2 (B), U1.13 (~RESET~)
/SCK: J1.3 (SCK), R7.2, U1.9 ((SCLK/PCINT1)PB1)
GND: C1.2, C2.2, C3.2, C4.2, C5.2, C6.2, C7.2, C8.2, C10.2, C11.2, C12.2, C13.2, C14.2, J1.6 (GND), SW2.1 (A), U1.5 (UGND), U1.15 (GND), U1.23 (GND), U1.33 ((~HWB~)PE2), U1.35 (GND), U1.43 (GND), U1.45 (PAD), U2.1 (GND), U3.1 (1~OE), U3.4 (2~OE), U3.7 (GND), U3.10 (3~OE), U3.13 (4~OE), X1.2, X1.4, XS1.6 (GND)
unnamed: C7.1, U1.17 (XTAL1), X1.1
unnamed: C8.1, U1.16 (XTAL2), X1.3
unnamed: C10.1, U1.42 (AREF)
unnamed: C11.1, SW3.2 (B), U2.3 (VI)
unnamed: R1.1, U3.12 (4A)
unnamed: R1.2, XS1.7 (DO/DAT0)
unnamed: R2.1, U3.2 (1A)
unnamed: R6.2, U3.9 (3A)
unnamed: R7.1, U3.5 (2A)
unnamed: U3.3 (1Y), XS1.3 (DI/CMD)
unnamed: U3.6 (2Y), XS1.5 (CLK)
unnamed: U3.8 (3Y), XS1.2 (CS/DAT3)
VBUS: C1.1, C2.1, C3.1, C4.1, C5.1, C6.1, J1.2 (VCC), R3.1, SW3.1 (A), U1.2 (UVCC), U1.14 (VCC), U1.24 (AVCC), U1.34 (VCC), U1.44 (AVCC)

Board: 2 copper layers, 26 parts (0 on the bottom side), 20 nets, no tracks yet.
